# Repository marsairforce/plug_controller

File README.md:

# A  solid state relay for duplex plug mains switching

I wanted to have an extension cord, with power distribution (many outlets), so like a power bar. On my desk. That I could conveniently switch on in an arbitrary way.

Here it is assembled in all of its glory

The rest of this page explains the thought process that got to this point.

Schematic and board layout were done using Kicad.

# License
[Creative Commons - Attribution - ShareAlike 3.0](LICENSE.md)

# WARNING

Disclimer. Danger. Working with mains AC power is dangerous. You can die. Your kids can die. Your pets can die. You can burn down your house. You can cause your neighbor's house to burn down when your house is burning down.

You have to know how to be safe.
* Never connect live AC mains to something without having all the conductors insulated.
* Be aware of the current carrying capacity of the components and wires you are using. Things fail badly when there is high voltages involved and you exceed the rated voltages. e.g. capacitors explode.
* Be aware of the thermal considerations of the compon you are using. Things that pass current will dissipate heat as they are in operation. When things get too hot, they burn. when they burn they cause other things to burn too.
* Always test AC switching things using a low voltage AC source, such as a transformer, or an isolation transformer where the current can be controlled before trying to plug your stuff in for the first time. short circuits can cause unexpected current or loading and this can cause things to explode or you can get a nasty shock, including, but not limited to death.

There are a lot of good articles and discussion on the Internet. Read up. Know what you need to do to be safe

Doing anything I do here is something you are doing at your own risk.

I am actively telling you to not do anything I am doing here.

# Background
For many years I have always assembled my own power distribution devices.

This goes back to 1990's era of computing where most peripheral devices had their own Class 2 plug in wall transformer (AKA brick) and the bulk of these things would cover several slots on the typical K-Mart power bar strips. So then you need to buy three power strips and chain them all together. And this is worse, both electrically and aesthetically.

Now I guess there are less peripherals that need big dumb bulky bricks. But I sort of appreciate the extra features I can achieve by having a customizable power strip. Like this most recent one I use on my workbench.

Some plugs have the half a plug, half a switch. So I can conveniently switch the thing off instead of having to (un)plug it every time. This is also useful for stopping phantom power loss, like the computer power brick when I am not at home.

The downside is lately I have more small desk appliances I want to have plugged in. Lamps. Solder stations. I would have enough plugs if it was not for half of my plugs being taken up by switches. And of course when your desk is a littered mess of several in progress project ideas you will never get around to finishing, it is somewhat inconvenient to have to reach over all this mess and find the right switch.  Of course it would be neat to have some other means to just control these plugs.  Like a system tray widget on my computer, a simple USB to GPIO device to control the switching of the plugs.

Of course it is awesome to build something that is "internet of things". Make a fun app to control a plug from anywhere in the world!.  Apps!! I could build a small wifi or bluetooth receiver into the plug box and have an elegant wireless control too.

Well, this is not quite there yet. I thought I would start with building just the switching part of things. Which technically is just a solid state relay. And to use regular wires to control it. Then then I can work on building integrations or wireless signalling, or apps, or even just a panel with legacy push buttons.

# Next steps

* I would like some feedback for how this is constructed. Is there anything I can do better?

* Measure the performance. How hot does the triac get under what AC load.

* Create a board with the updates and feedback.

* I would like to get my circuit board CSA approved, or UL certified. So then it could be used in like my office without causing anyone undue concern.

* Design a 3.3v power supply, or use an existing module thta does this, so I can stuff small wireless or bluetooth micro controller into the plug. maybe a separate circuit board for this. Though I kind of like the idea of "just a plug control", it would be more practical in a general use to have these around a house and not just on my workbench.

# Theory
I really did not consider using mechanical relays because of their bulky size. I wanted something that could fit into a regular metal plug box.  There are a lot of [relay modules](https://www.cytron.io/p-bb-relay-5v-02), [shields](https://www.seeedstudio.com/Relay-shield-V2.0-p-1376.html).

Though this feels somewhat incomplete.
* There is no fuse.
* The low voltage connections is just breadboard jumper style header pins. Not a very robust connector.
* It needs 5V, but I want to use 3.3v.
* You need to drive an active low signal to control the relay.
* The Arduino shield is down right dangerous for 120V use, being directly on top of the Arduino like that.
* Physically these are too large to fit inside a regular metal plug box.

I am sure these are good for some things, lower voltage switching like for a HVAC thermostat. Or applictions where you really want a normally closed feature. Or for setting up some experiements to demonstrate or learn like for a lab or classroom setup.

They just didn't feel like a good fit for what I wanted to do here.

Really it is more elegant to use Triac device with an opto isolator. This is the same feature and behavior as a solid state relay. Ok. fine. Just get a couple nice solid state relays. Done. Nothing to see or do here.

Well. Its just that a regular solid state relay is [quite expensive](https://www.digikey.ca/product-detail/en/sensata-crydom/PF240D25/CC1341-ND/278899).  And the dual solid state relays are even [more expensive](https://www.digikey.ca/product-detail/en/sensata-crydom/UPD2415D-10/CC2483-ND/2177128). Although. Just having to design a PCB that makes use of these already RU certified parts. Someone has done the work to try to compute the current and thermal carrying abilities (see below). It is a compelling reason to just buy vs build. A [popular youtuber](http://www.instructables.com/id/Make-Your-Own-Solid-State-Relay/) also agrees that in this case it is really better to buy a solid state relay instead of trying to build your own. Like I am doing here. So maybe just look into finding one we can buy.

Oh.. You are still reading this. Ok. Onward.

I did find some other projects for an [Arduino Triac Shield](https://forum.arduino.cc/index.php?topic=24335.0). But that looks horribly dangerous again with the high voltage there mixed up and exposed with the low voltage stuff. And again with the too large to fit into a metal plug box.
There was a later version with the separate board, but again this only has 1 triac.

I took a few minutes to read up on what kinds of Triacs are out there, and found I like these [STMicroelectronics Snubberless series Triacs](http://www.st.com/content/ccc/resource/technical/document/application_note/ca/ef/9d/1e/4a/9f/47/69/CD00003865.pdf/files/CD00003865.pdf/jcr:content/translations/en.CD00003865.pdf).

* These devices are readily available on [Digikey](https://www.digikey.ca/product-detail/en/stmicroelectronics/T2535-800G-TR/497-10581-1-ND/2294945
)
* They are rated for 25A. With peak surge of 260A for 16 ms (e.g. inrush current)
* Rated for repetitive peak off-state voltage of 800V.

So this should be safe for how we plan to use it.  The next thing to consider is how hot this will get when operating.

* Tj = 125 °C (Operating junction temperature)
* Rth(j-c) is 0.8 °C/W
* Rth(j-a) is 45°C/W.

Their [thermal management for handling and mounting](http://www.st.com/content/ccc/resource/technical/document/application_note/42/4a/77/9a/f5/58/43/77/CD00004000.pdf/files/CD00004000.pdf/jcr:content/translations/en.CD00004000.pdf) document recommends for the D2PAK packaging using a FR4 board with copper heat spreader area, and filled copper thru holes, or an additional heatsink.

The data sheet recommends only currents up to 8A for a good FR4 board design. Since I don't have the filled copper thru holes, I would say the actual current I can safely support with my board is  going to be much less.

Trying to think about this, for room temperature use

* Ta = 20 °C
* Tj = 125 °C
* Rth(j-a) = 50 °C/W

With the junction temperature modelled as `Tj = Ta + (P * Rth(j-a))`

Then `P = (Tj - Ta) / Rth(j-a)`

Or, with no heat sink, P = 2.1W . That feels wrong to me. But then further [reading](http://www.farnell.com/datasheets/1760777.pdf), yes it is regular to expect 2W heat dissipation for surface mount triacs.

Remember too, that thermal requirements for the triac will be the power loss inside the triac, not the power to the AC load device.  From the datasheet the peak on-state voltage drop, VTM, is the voltage across the device while it is on-state. It is specified at the peak current corresponding to the IT(RMS) current of the device. This voltage to determine the power dissipated by the triac.

So for these triac devices,

* VTM = 1.55 V

So then, if we want to keep power dissipation down to 2 W, the max current we can pass is about 1.3 A. Or about 150 watts.

The recommended approach for surface mount components is to use Insulated Metallic Substrate (IMS). IMS offers enhanced thermal characteristics as is a substrate consisting of three different layers:
* base material which is available as an aluminum or a copper plate
* thermal conductive dielectric layer
* copper foil, which can be etched as a circuit layer.

Using an IMS board should reduce the Rth(j-a) from 50 °C/W to 8 °C/W.  Which should then allow the triac to dissipate 13 W of power, or about 8 A

This is not something I have access to at OSHPark. This other place [Twisted Traces](https://www.twistedtraces.com/products/prototype-panel/ims-insulated-metal-substrate-pcb) appears to support IMS boards. We have to order a single panel, that goes for $320 USD, which for this board size will be about 26 boards or cost to about $12 per board. But this will allow us to handle up towards 900 W loads.

So it is becoming clear to me now why actual solid state relays are so large. They are mostly heat sinks and electrical isolation.

Another [data sheet](https://www.farnell.com/datasheets/1760767.pdf) sais "Please note that the actual thermal resistance will be reduced by other, non-dissipating components in close proximity to the triac, while it will be increased by any components that dissipate power in the presence of the triac. It is essential therefore to measure the prototype to discover the true thermal performance."

Having to also consider there are two triacs near each other. So this will influence their heat dissipation abilities right.

So I need to apply some test loads to the device and see how hot it gets and how fast.  I will need  thermal sensor (those tools that use the infrared light to measure temperature) and a load device.  I do not have a good electrical load testing tool either. All i have is a heat gun, which has low (~5A) and hight (~9.5A) current draw.

# Assembly
This is definitely one of those things where it requires a lot more effort and consideration to take a project from just an idea idea to a something that is "finished" product. Or at least, something that is safe to use and actually useful.

This is the kind of stuff I didn't get to learn in school. Maybe I didn't take the right courses. But in any case some stuff was not obvious to me until I tried it. In some cases I did not even know what I needed to do. It took me a few tries to get it right. Sometimes there were failures. I figured I would chronicle the revisions here, as some of the things that came up were not obvious to me. So they might be a good learning tool for others.

# V1.1
Small improvements on the v1.0 build:

* The connection of the opto triac to the A1 and G pins of the T25 was wrong. Updated footprint, schematic, and new board layout to fix this.

* The fuse holder footprint was differnt from the fuse holder clips I had ordered. The same family. Just curiously rotated 90°. I worked around it by ordering some more fuse holder clips. But really this was another footprint selection bug. Now using the footprint for the fuse holders I have.  The ones that are in use now are slightly lower profile, so the fuse is held closer to the board, leaving the slightly more room in the box for the plug.

* The resistor from opto triac could be larger. Reading the datasheet, using 300 ohm is well within the current capabilities of both the MOC3063M and the T25. But It is perhaps more current than is required.  When patching the V1.0 board with a thru hole resistor I found we can use up to about 1K total resistance.

* Relocated the ground terminal connection to bottom of the low voltage side. It was near the terminal block and in the way if we wanted to use [MTA-100 series](https://www.digikey.ca/products/en?FV=ffec1142) connectors for internal wiring.

* Using OSHPark 2 oz copper service http://docs.oshpark.com/services/two-layer-hhdc/. It is better suited for current capacity.

# V1.0

So with the idea in mind and much reading of the datasheets and internet posts, set off to design. The triac application note demonstrates how they could be used as a solid state state relay, by fronting them ith an opto isolator with zero crossing detection and triac output.

We have a connector there for AC ground to be also our ground.

This is actually two swiches. The idea being that in a standard duplex plug there are two halves (top and bottom). So that we can provide individual switching to each half. Which will allow us to plug two lights into a single duplex plug.

The inputs to the opto isolator is a constant current source provided by the two NPN transistors. Q1 is activated when there is enough current flowing through R3 to provide a voltage drop of the about 0.6V to cause Q1 to turn on, which works to turn off Q3. This allows us to have a wide range of input voltage (2 to aobut 30V) but without having to worry about using a current limiting resistor that will just dissipate the extra voltage as heat.  I like the idea of my electrical things not getting too hot of course. Probably it will be just used for 3.3V to 5V from a microcontroller.

The board can be laid out small enough to fit inside a metal duplex outlet style box. So that we can provide control wires into the box.

I was invisioning an extension cord with the metal plug box on the end with this controller board inside the metal box.

This keeps all of the 120V AC inside the extension cord and outlet box. We do not need to have 120V wires going out of the box to our circuit board. Which is a good thing here, since we are working with both water and electricity.

So to use this we will just need 2 digital IO pins from the micro controller.

In this case, It was challenging for me to breadboard this, because the pieces are all surface mount. And I have reservations about using 120V AC on a solderless breadboard. Instead I had some circuit boards built using OSHPark and then assembled the pieces.

This first version I managed to mix up the A1 and A2 pin outs for the triac

I believe the issue was I chose the standard footprint for "a triac" with the pin out A,A,G. But maybe this D2PAK type package has a different pin numbering than the TO-220 type case?   So I updated the schematic and board layout for next time.

It turns out this is super important. We basically require a voltage across the A2 and G. not the A1 and G as I have it (the images in this document are still wrong. The kicad project is updated).

So fixing the circuit board with some bodge resistors and cutting the trace they work now. Remember. this is a prototype.  I also tested this using a 120V to 12VAC transformer, and test lit up an old automotive headlamp I had in a junk bin. Before graduating to try to test switch AC mains things.

Note there is a cut out under those opto isolators, so as to improve the isolation between the low voltage and high voltage side. I also have the metal box ground connecting to the ground plane on the low voltage side. There is no ground plan on the AC side.  Just the wide traces and the pad for the triacs which goes directly to these terminal connectors.

With the board ready to go and, its time to assemble into the metal plug box.

The plug itself has that metal bridge bar between the top and bottom outlets cut so that we can power each top and bottom half individually.

I used these nice crimp and spade connectors as according to electrical code we can't be soldering these wires. This is probably the risk of mechanical separation and causing high resistance of the solder joint causing a fire. I didn't have to, but also used fork terminals on the wires for the screw to the plug, it just makes for a nicer wiring job, and now there are no possibility of stray wires coming out from under the screw terminals.

According to electrical code, low voltage wires can not exist within the same box, conduict, or package as high voltage wires. With the exception if you are making an all in one powered plug in wireless access point. So for now that is why I have that hole in the box, the screw terminals to the low voltage wires hook up out of that hole. So then the only wires inside this box are the 14 gauge 12V AC wires.

The low voltage side of things was designed to be on the neutral side of the plug. The hot side of the plug being on the side where the wire and terminal connectors are.

The board is mounted inside the metal plug box by drilling some holes into the metal box. And using 1/4 inch hex aluminum stand offs. I think I placed the holes far enough away from the AC points on the circuit board to be OK. Though I covered the solder side (the side that is facing down towards the metal box) with some electrical tape just in case.  I use nylon screws into the metal standoffs so its less metal surface on the top of the circuit board. They seem to be able to get a good snug fit and have that feeling they won't come loose on their own.

Here I do not have a physical baffle between the low voltage and high voltage side. Though the precautions I took above are likely ok for my use for now.

The only thing I do not like about this is the need to have an actual wire wired up to the box. I would prefer to have some kind of connector. I was thinking RJ-11 because this control cable is old flat phone wire I had on hand.

The boards OSHPark offers are 1 oz (1.4mil) FR4 boards that are 1.4mm thick http://docs.oshpark.com/services/two-layer/ These are not the best for thermal conductuctivity.   I should really have used their 2 oz copper product http://docs.oshpark.com/services/two-layer-hhdc/

This board was designed following the footprint layout, but not doing the maths for the thermal requirements for the triacs first. After crunching the numbers these devices in their configuration are good for up to about 2W of power dissipation. Which is 150 watts of load per device. Which is of course good enough for LED desk lamps, soldering stations, glue guns, oscilliscope, usb charger bricks, TV, small computing appliances. But not so much for heat guns, spot welders. Though these are intermediate use.  Again, more testing will help us to see.

To be able to get the triacs to handle more power, they need better heatsinks. I could have put more copper on the other side of the board and used via stitching to help transfer the heat. The downside of this of course is there is more electrically live surface area we have to be aware of. Though the solder mask does offer some protective coating.

There are these little [clip on heatsinks](https://www.digikey.ca/product-detail/en/wakefield-vette/217-36CTE6/345-1099-ND/1033769) for these TO-263 package. Maybe should see how these help too. They have a thermal resistance of 55.00 °C/W . So this will improve the heat dissipation abilities of the triac, allowing it to handle more power. But how much more?  Stupid maths and formulas.Not sure how to work this.  Maybe I'll just try them. But need to borrow a temperature sensor first.

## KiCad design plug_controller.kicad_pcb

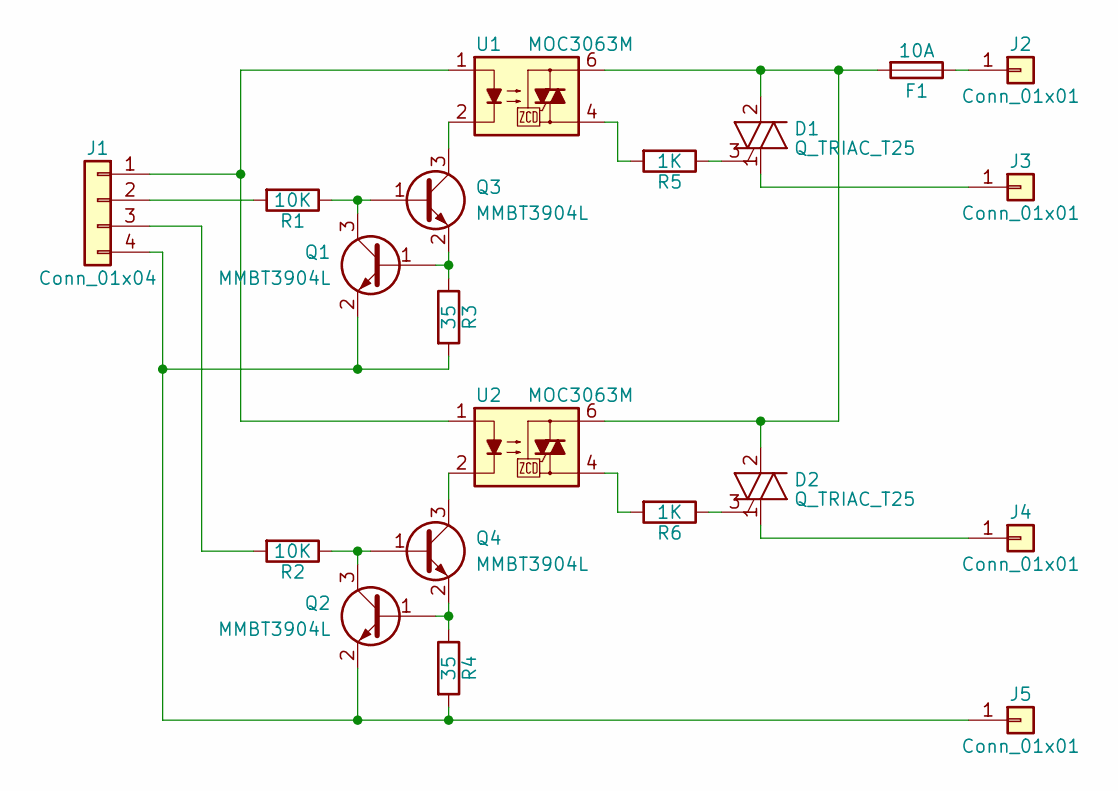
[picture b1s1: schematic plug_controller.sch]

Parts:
D1, D2: Q_TRIAC_T25; D2PAK
F1: 10A; Fuseholder5x20_horiz_open_lateral_Type-II
J1: Conn_01x04; Molex_KK-6410-04_04x2.54mm_Straight
J2, J3, J4, J5: Conn_01x01; TAB_0.250_SOLDER
Q1, Q2, Q3, Q4: MMBT3904L; SOT-23
R1, R2: 10K; R_0603
R3, R4: 35; R_0603
R5, R6: 1K; R_0603
U1, U2: MOC3063M; 6-SMD_Gullwing

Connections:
unnamed: D1.1 (A2), J3.1
unnamed: D1.2 (A1), D2.2 (A1), F1.2, U1.6, U2.6
unnamed: D1.3 (G), R5.1
unnamed: D2.1 (A2), J4.1
unnamed: D2.3 (G), R6.1
unnamed: F1.1, J2.1
unnamed: J1.1, U1.1, U2.1
unnamed: J1.2, R1.2
unnamed: J1.3, R2.2
unnamed: J1.4, J5.1, Q1.2 (E), Q2.2 (E), R3.2, R4.2
unnamed: Q1.1 (B), Q3.2 (E), R3.1
unnamed: Q1.3 (C), Q3.1 (B), R1.1
unnamed: Q2.1 (B), Q4.2 (E), R4.1
unnamed: Q2.3 (C), Q4.1 (B), R2.1
unnamed: Q3.3 (C), U1.2
unnamed: Q4.3 (C), U2.2
unnamed: R5.2, U1.4
unnamed: R6.2, U2.4

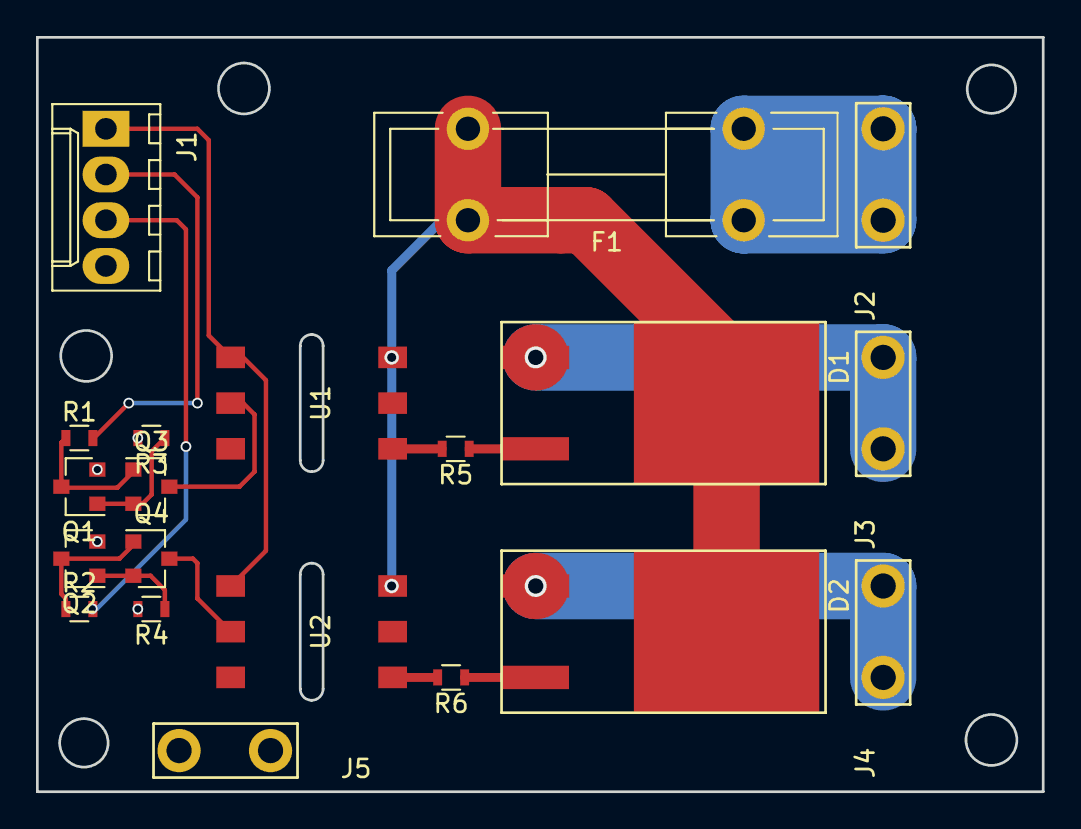
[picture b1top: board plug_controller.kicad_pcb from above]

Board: 2 copper layers, 55.9 x 41.9 mm, 20 parts (0 on the bottom side), 18 nets.

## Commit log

2018-05-12 inital commit
    import the files on documents folder from laptop
2018-05-12 link to license on the readme
2018-05-12 update PCB layout. update documentation.
    some thoughts and consideration for thermal heat dissipation requirements and max power this device can handle
2018-05-12 fix the title
2018-05-12 typos
2018-05-12 learn about what Vtm is.
2018-05-12 more thoughts on heat absorption
2018-05-12 add documentation about buying your on SSD
2018-05-13 small clean up for wordings
